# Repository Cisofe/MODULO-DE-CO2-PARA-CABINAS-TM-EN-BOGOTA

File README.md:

# MODULO-DE-CO2-PARA-CABINAS-TM-EN-BOGOTA
## Proyecto de ingeniería

El módulo de CO2 para buses TM es un prototipo ideado para proporcionar datos para análisis y control de la calidad del aire en las cabinas de buses troncales del sistema BRT de la ciudad de Bogotá, Colombia. El dispositivo permite que los estadísticos y analistas de datos obtengan información de la temperatura, humedad y concentración de CO2 en el interior de los vehículos, además de automatizar el funcionamiento del sistema de ventilación de acuerdo a los valores de concentración de CO2. Las personas que conmutan a diario en los buses también podrán acceder a datos recientes de la calidad del aire en su cabina, lo que busca proporcionar más transparencia y aumentar el interés de los usuarios en el tema. Asimismo, esto podría incidir en el incremento de estudios sobre la aglomeración de TransMilenio y las condiciones del aire en sistemas de transporte masivo público y cómo influyen en el pasajero.

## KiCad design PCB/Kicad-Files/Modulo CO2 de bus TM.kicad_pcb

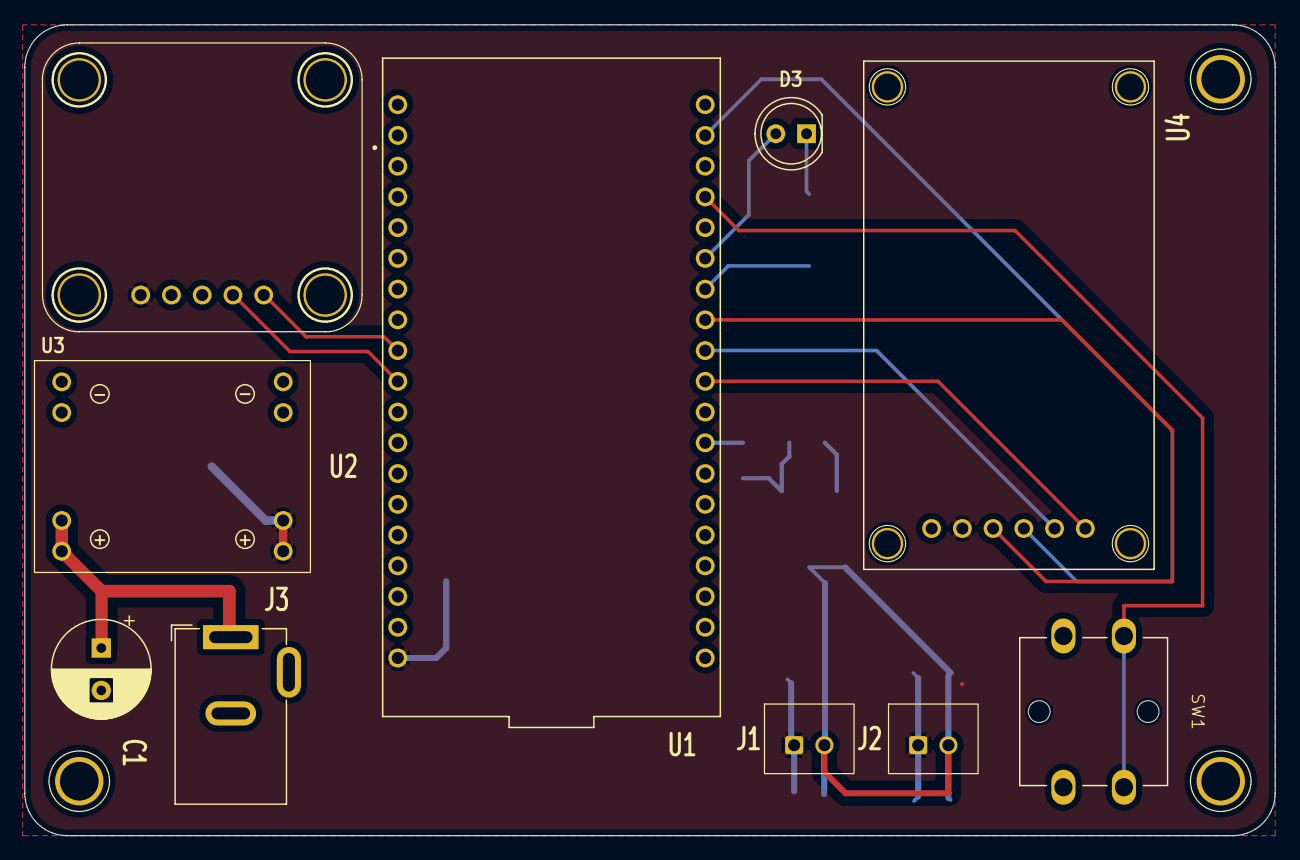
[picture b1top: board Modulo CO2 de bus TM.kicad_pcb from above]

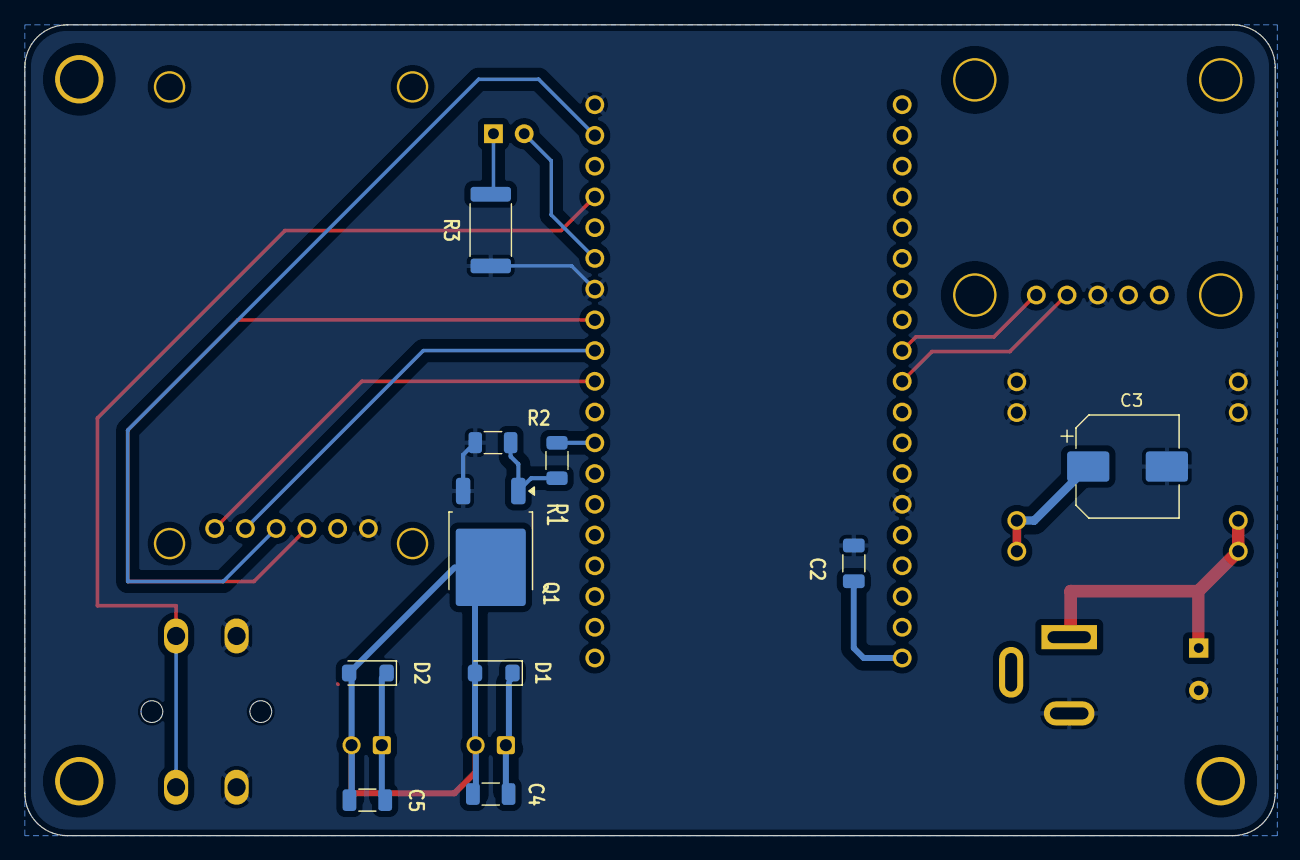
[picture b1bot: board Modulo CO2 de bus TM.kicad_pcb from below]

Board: 2 copper layers, 103.3 x 67.0 mm, 20 parts (10 on the bottom side), 15 nets.

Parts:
C1: C_Polarized; Cap_Elec_THT_8 mm 3,50 mm
C2, C4, C5: 0.1uF 450V; C_1206_3216Metric
C3: 470uF 16V; CP_Elec_8x10
D1: SS34FA; D_SOD-123FA
D2: SS34; D_SOD-123FA
D3: LED; LED_5.0mm
J1, J2: JST_XH_2P_Male; JST_XH_2P_MALE_7.4x5.75mm
J3: Barrel_Jack_Switch; BarrelJack_Sw
Q1: FDD8580; TO-252-2
R1: 100 Ω; R_1206_3216Metric
R2: 10K Ω; R_1206_3216Metric
R3: 120 Ω; R_2512_6332Metric
SW1: SW_SPST; B3F-4055 12x12x7,3
U1: DEVKIT_V1_ESP32-WROOM-32; MODULE_ESP32-DEVKITC-32D
U2: MODULE_Buck-MP1584EN; MODULE_Buck5V1.5A_MP1584EN
U3: MODULE_SCD40_Adafruit
U4: Module_MicroSD-Adapter-Reader; SD_Card_Module

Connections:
/CS_SDCARD: U1.29 (IO5), U4.1 (CS)
/Gate: R1.2, U1.27 (IO16)
/I2C_SCL: U1.10 (IO26), U3.4 (SCL)
/I2C_SDA: U1.9 (IO25), U3.5 (SDA)
/MISO: U1.31 (IO19), U4.4 (MISO)
/MOSI: U1.37 (IO23), U4.3 (MOSI)
/SCK_SDCARD: U1.30 (IO18), U4.2 (SCK)
GND: C1.2, C2.2, C3.2, J3.2, Q1.3 (S), R2.1, R3.1, SW1.2 (B), U1.14 (GND1), U1.32 (GND2), U1.38 (GND3), U2.1 (IN-), U2.3 (OUT-), U3.3 (GND), U4.6 (GND)
unnamed: C4.1, C5.1, D1.2 (A), D2.2 (A), J1.2 (LOAD_NEG), J2.2 (LOAD_NEG), Q1.2 (D)
unnamed: D3.2 (A), U1.33 (IO21)
unnamed: D3.1 (K), R3.2
unnamed: Q1.1 (G), R1.1, R2.2
unnamed: SW1.1 (A), U1.35 (TXD0)
unnamed: C1.1, J3.1, U2.2 (IN+)
VDD: C2.1, C3.1, C4.2, C5.2, D1.1 (K), D2.1 (K), J1.1 (+5V), J2.1 (+5V), U1.19 (EXT_5V), U2.4 (OUT+), U3.1 (Vcc), U4.5 (Vcc)

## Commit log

2025-07-20 Create Codigo
    Carpeta para adjuntar código
2025-07-20 Delete Codigo
    Delete
2025-07-20 Create init.txt
    Initialize folder
2025-07-20 Create init.txt
    Initialize
2025-07-20 Upload
2025-07-20 Delete
2025-07-20 Change
2025-07-23 Read
2025-07-23 pcb3d
2025-07-23 Evidencias soldadura
2025-07-23 boceto
2025-07-23 Rename imagen prototipo.jpg to evidencia_cabina_escala.jpg
2025-07-23 Rename evidencia_cabina_escala.jpg to Evidencia_cabina_escala.jpg
